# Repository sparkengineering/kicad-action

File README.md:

# kicad-action

GitHub Action to automate KiCad tasks, e.g. check ERC/DRC on pull requests or
generate production files for releases.

## Features

- Run Electrical Rules Check (ERC) on schematic
- Run Design Rules Check (DRC) on PCB
- Generate PDF and BOM from schematic
- Generate Gerbers ZIP from PCB
- Generate raytraced board images

## Example

```yaml
on: [push]

jobs:
  kicad_job:
    runs-on: ubuntu-latest
    name: My KiCad job
    steps:
      - name: Checkout
        uses: actions/checkout@v4

      - name: Export production files
        id: production
        uses: sparkengineering/kicad-action@v4
        if: '!cancelled()'
        with:
          kicad_sch: my-project.kicad_sch
          sch_pdf: true # Generate PDF
          sch_bom: true # Generate BOM
          kicad_pcb: my-project.kicad_pcb
          pcb_gerbers: true # Generate Gerbers

      # Upload production files only if generation succeeded
      - name: Upload production files
        uses: actions/upload-artifact@v4
        if: ${{ !cancelled() && steps.production.conclusion == 'success' }}
        with:
          name: Production files
          path: |
            ${{ github.workspace }}/sch.pdf
            ${{ github.workspace }}/bom.csv
            ${{ github.workspace }}/gbr.zip

      - name: Run KiCad ERC
        id: erc
        uses: sparkengineering/kicad-action@v4
        if: '!cancelled()'
        with:
          kicad_sch: my-project.kicad_sch
          sch_erc: true

      - name: Run KiCad DRC
        id: drc
        uses: sparkengineering/kicad-action@v4
        if: '!cancelled()'
        with:
          kicad_pcb: my-project.kicad_pcb
          pcb_drc: true

      # Upload ERC report only if ERC failed
      - name: Upload ERC report
        uses: actions/upload-artifact@v4
        if: ${{ failure() && steps.erc.conclusion == 'failure' }}
        with:
          name: erc.rpt
          path: ${{ github.workspace }}/erc.rpt

      # Upload DRC report only if DRC failed
      - name: Upload DRC report
        uses: actions/upload-artifact@v4
        if: ${{ failure() && steps.drc.conclusion == 'failure' }}
        with:
          name: drc.rpt
          path: ${{ github.workspace }}/drc.rpt
```

See this example working in the action runs of this repository.

## Configuration

| Option             | Description                                     | Default                      |
|--------------------|-------------------------------------------------|------------------------------|
| `kicad_sch`        | Path to `.kicad_sch` file                       |                              |
| `sch_erc`          | Whether to run ERC on the schematic             | `false`                      |
| `sch_erc_file`     | Output filename of ERC report                   | `erc.rpt`                    |
| `sch_pdf`          | Whether to generate PDF from schematic          | `false`                      |
| `sch_pdf_file`     | Output filename of PDF schematic                | `sch.pdf`                    |
| `sch_bom`          | Whether to generate BOM from schematic          | `false`                      |
| `sch_bom_file`     | Output filename of BOM                          | `bom.csv`                    |
| `sch_bom_preset`   | Name of a BOM preset setting to use             |                              |
| `report_format`    | ERC/DRC report file format (`json` or `report`) | `report`                     |
|                    |                                                 |                              |
| `kicad_pcb`        | Path to `.kicad_pcb` file                       |                              |
| `pcb_drc`          | Whether to run DRC on the PCB                   | `false`                      |
| `pcb_drc_file`     | Output filename for DRC report                  | `drc.rpt`                    |
| `pcb_gerbers`      | Whether to generate Gerbers from PCB            | `false`                      |
| `pcb_gerbers_file` | Output filename of Gerbers                      | `gbr.zip`                    |
| `pcb_image`        | Whether to render the PCB image                 | `false`                      |
| `pcb_image_path`   | Where to put the top.png and bottom.png         | `images`                     |
| `pcb_model`        | Whether to export the PCB model                 | `false`                      |
| `pcb_model_file`   | Output filename of PCB model                    | `pcb.step`                   |
| `pcb_model_flags`  | Flags to add when exporting STEP files          | see [action.yml](action.yml) |

## Roadmap

- [ ] Add support for more configuration options, e.g. BOM format or Gerber layers
- [ ] Add a way to specify KiCad version to use
- [ ] Better detect if steps of this action fail
- [ ] Find a better way to enforce the default output files extensions depending on the format requesed

## Contributing

Contributions, e.g. in the form of issues or pull requests, are greatly appreciated.

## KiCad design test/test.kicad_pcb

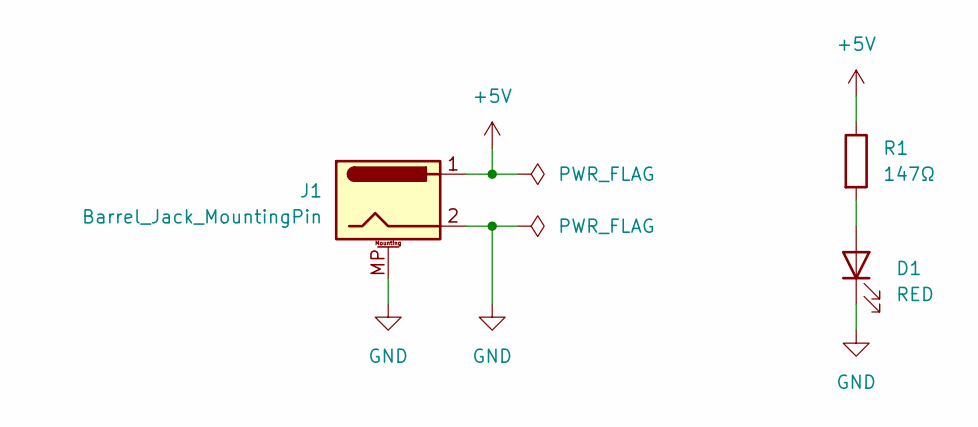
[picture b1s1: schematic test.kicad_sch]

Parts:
D1: RED; LED_D5.0mm; Mouser No 710-151051RS11000
J1: Barrel_Jack_MountingPin; BarrelJack_CUI_PJ-063AH_Horizontal; Mouser No 490-PJ-063AH
R1: 147Ω; R_Axial_DIN0207_L6.3mm_D2.5mm_P10.16mm_Horizontal; Mouser No 594-MBB02070C1470FC1

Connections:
+5V: J1.1, R1.1
GND: D1.1 (K), J1.2, J1.MP (MountPin)
unnamed: D1.2 (A), R1.2

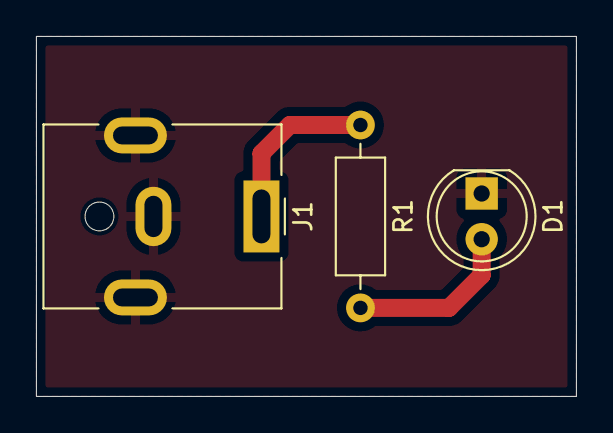
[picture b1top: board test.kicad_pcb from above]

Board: 2 copper layers, 30.0 x 20.0 mm, 3 parts (0 on the bottom side), 3 nets.

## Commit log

2024-05-19 Fix example
2024-05-19 Bump KiCad version
2024-05-19 Increment version number
2024-09-03 set the kicad version to always be the latest 8.0 version
2024-09-03 add an 'output file extension' action input
2024-09-03 make the test ERC generate a json file
2024-09-04 rename input variable
2024-09-04 fix test action
2024-09-08 Bump version
2024-10-23 added rendering
2024-10-23 added rendering to test
2024-10-23 debug time
2024-10-23 fix image output path
2024-10-23 more debugging
2024-10-23 make image folder relative to project folder
2024-10-23 remove debugging output
2024-11-09 set entrypoint to fail more eagerly
2024-11-09 freeze kicad version for stability
    As it turns out kicad nightly breaks sometimes, so freezing it prevents
    that. Really we should be using stable, but 3d-rendering won't be
    stable for a few months
2024-11-09 Fix kicad version to something that actually works
2024-11-09 export 3d model
2024-11-09 fix typos
2024-11-09 moved to a different branch so I can quash this later
2024-11-09 debugging the test which fails for some reason
2024-11-09 BOM generation is broken for some reason. time to wait a few months for that I guess.
2024-11-10 add option to set flags to adjust model size
2025-02-25 Kicad 9.0 has released. Need to merge back upstream eventually.
2025-02-25 updated test so that it doesn't fail
2025-03-19 clean up some stuff for upstream merge.
2025-03-19 fix dockerimage to use valid image
2025-03-19 Add raytraced image output (#4)
    * added rendering
    * added rendering to test
    * debug time
    * fix image output path
    * more debugging
    * make image folder relative to project folder
